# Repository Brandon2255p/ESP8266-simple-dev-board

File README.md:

# ESP8266-simple-dev-board
This is a simple breakout of the ESP8266-03 which is perfect for development. It includes a 3V3 regulator and header pins for 5V input. It also has Rx Tx pins for connection to an external TTL serial device. <br>

To change the schematic or board you will need to use Eagle Cad.<br>
<bl>
The current BOM is:
<li>1 x ESP8266-03</li>
<li>7 x 1K SMD Resistor (0805)</li>
<li>2 x Zero-ohm SMD Resistor (1206)</li>
<li>2 x SMD Tactile Switch</li>
<li>1 x 3V3 LDO - CP1117E33A</li>

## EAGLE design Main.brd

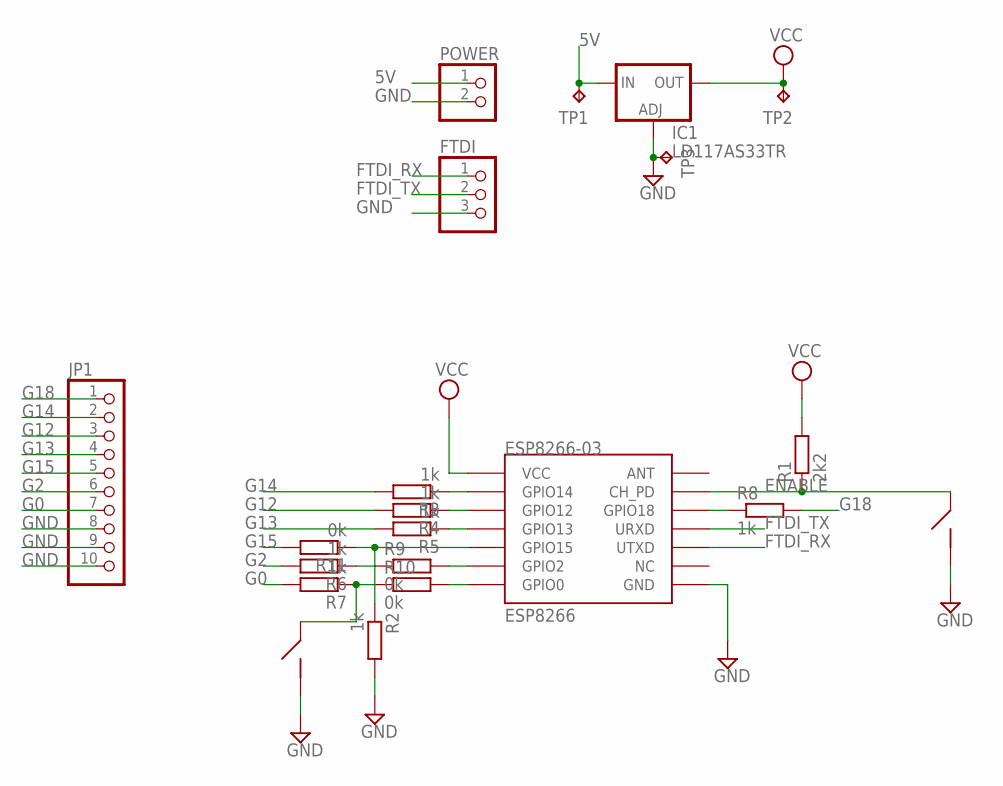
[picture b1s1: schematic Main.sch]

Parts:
ESP8266-03: ESP8266; ESP03
FTDI: PINHD-1X3; 1X03
IC1: LD117AS33TR; SOT223
JP1: PINHD-1X10; 1X10
POWER: PINHD-1X2; 1X02
R1: 2k2; M0805
R2, R3, R4, R5, R6, R7, R8: 1k; M0805
R9, R10: 0k; R1206
R11: 0k; M0805
TP1, TP2, TP3: TPB1,27; B1,27
U$1, U$2: TACTILE; DTSM31N

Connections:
5V: IC1.3 (IN), POWER.1, TP1.TP
ENABLE: ESP8266-03.CH_PD, R1.1, U$2.P$1
FTDI_RX: ESP8266-03.UTXD, FTDI.1
FTDI_TX: ESP8266-03.URXD, FTDI.2
G0: JP1.7, R7.2
G2: JP1.6, R6.2
G12: JP1.3, R4.2
G13: JP1.4, R5.2
G14: JP1.2, R3.2
G15: JP1.5, R11.2
G18: JP1.1, R8.2
GND: ESP8266-03.GND, FTDI.3, IC1.1 (ADJ), JP1.8, JP1.9, JP1.10, POWER.2, R2.2, TP3.TP, U$1.P$2, U$2.P$2
unnamed: ESP8266-03.GPIO15, R2.1, R11.1
unnamed: ESP8266-03.GPIO2, R9.2
unnamed: ESP8266-03.GPIO0, R10.2
unnamed: ESP8266-03.GPIO18, R8.1
unnamed: ESP8266-03.GPIO12, R4.1
unnamed: ESP8266-03.GPIO13, R5.1
unnamed: ESP8266-03.GPIO14, R3.1
unnamed: R7.1, R10.1, U$1.P$1
unnamed: R6.1, R9.1
VCC: ESP8266-03.VCC, IC1.4 (OUT), R1.2, TP2.TP

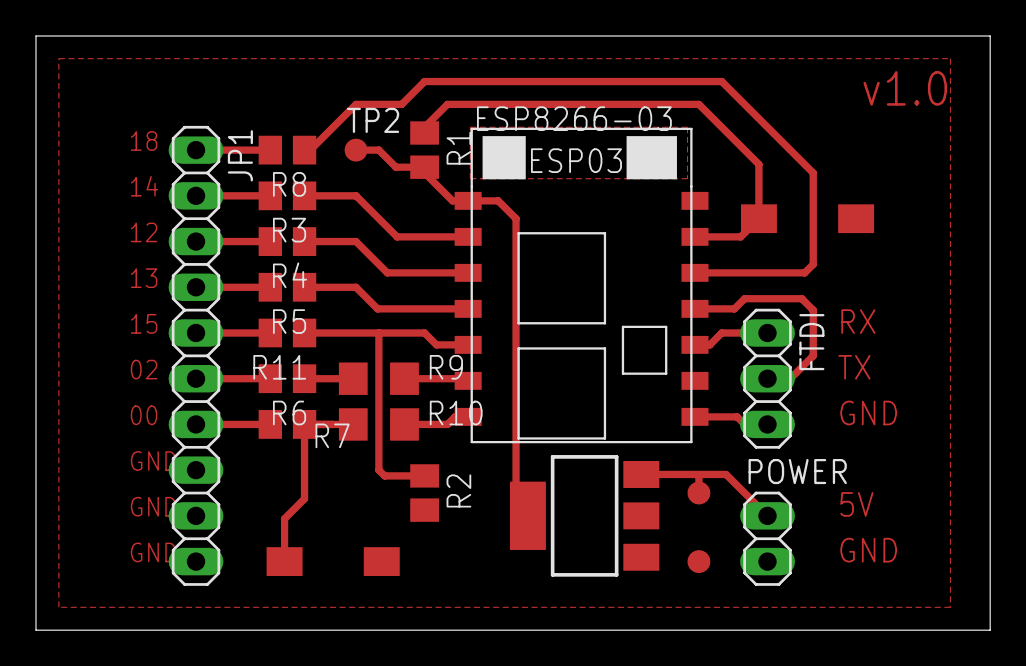
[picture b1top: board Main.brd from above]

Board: 2 copper layers, 53.0 x 33.0 mm, 21 parts (0 on the bottom side), 22 nets.

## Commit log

2016-07-10 Added V1.0
    This is the initial commit of a complete minimal ESP8266 circuit board
2016-07-10 Added ESP8266 board library as a submodule
2016-07-10 Added a cutout region under the antenna so that no ground plane is placed there
2016-07-11 Added BOM
    Added some of the BOM items
